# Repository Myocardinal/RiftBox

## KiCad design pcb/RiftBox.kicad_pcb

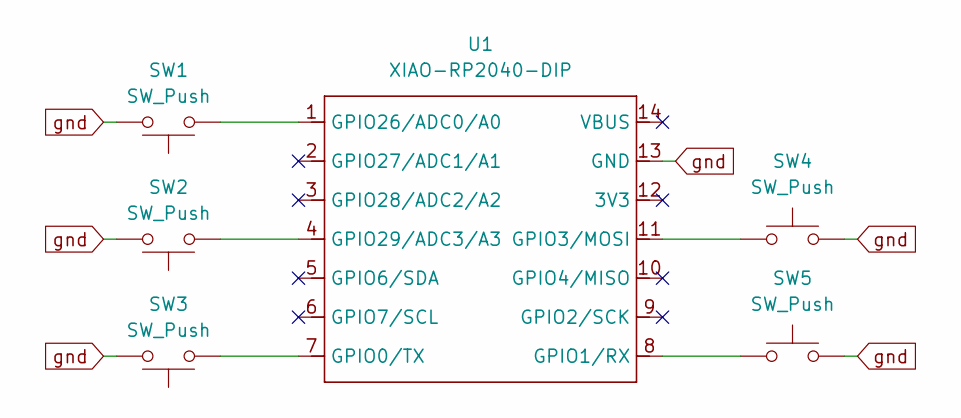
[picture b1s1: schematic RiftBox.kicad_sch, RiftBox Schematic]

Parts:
SW1, SW2, SW3, SW4, SW5: SW_Push; Shady JST XH 1x2 2.54 mm
U1: XIAO-RP2040-DIP

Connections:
unnamed: SW3.1, U1.7 (GPIO0/TX)
unnamed: SW5.1, U1.8 (GPIO1/RX)
unnamed: SW4.1, U1.11 (GPIO3/MOSI)
unnamed: SW1.1, U1.1 (GPIO26/ADC0/A0)
unnamed: SW2.1, U1.4 (GPIO29/ADC3/A3)
gnd: SW1.2, SW2.2, SW3.2, SW4.2, SW5.2, U1.13 (GND)

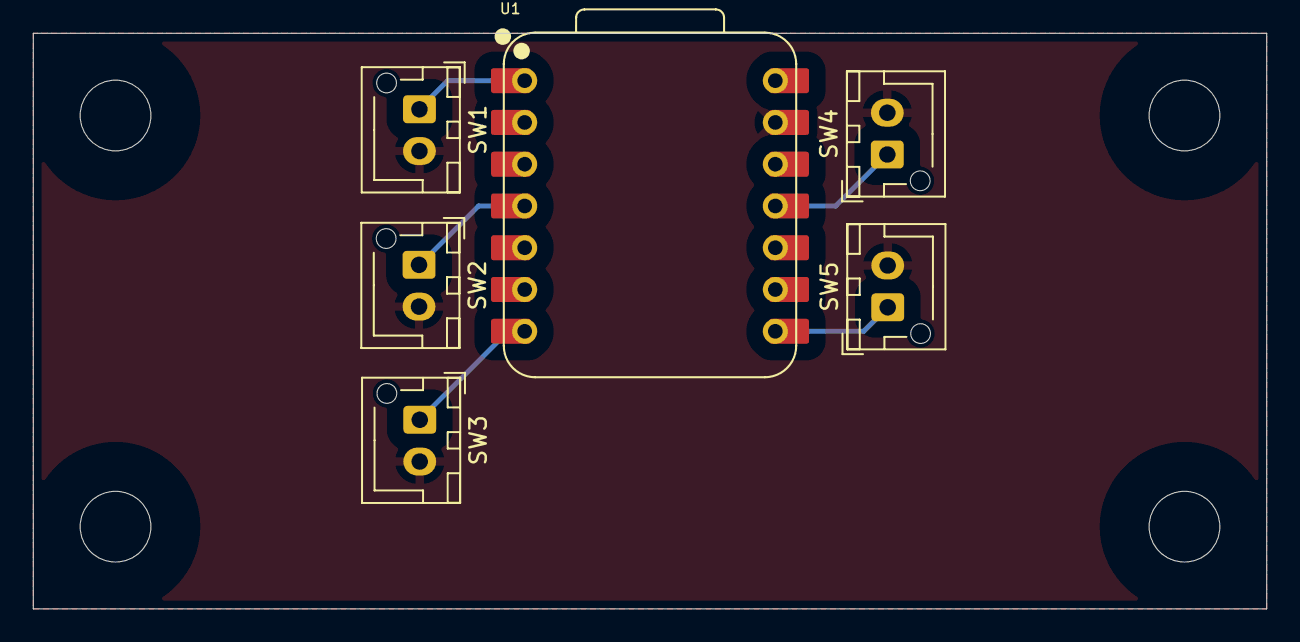
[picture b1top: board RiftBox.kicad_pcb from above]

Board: 2 copper layers, 75.0 x 35.0 mm, 6 parts (0 on the bottom side), 6 nets.

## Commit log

2025-03-15 Added PCB design
2025-03-15 Removed uncessecary kicad library
2025-03-15 Removed backups folder from repo
2025-03-24 PCB arrived and soldered, testing first prototype. Super high latency, so i'll switch to an existing solution instead
2025-04-04 It's working!! but not sure how much latency the arduino code is slurping up
